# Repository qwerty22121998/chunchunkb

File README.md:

# CHUNCHUN

Wireless split ortholinear keyboard with 70 keys, 2 nice!view displays, 2 rotary encoders.

Original inspirated by Sofle keyboard, but I want to add more keys (F-rows) and ortholinear layout. I also want to add 2 nice!view displays and 2 rotary encoders for better user experience.

## Images

`TBA`

## Specifications

- 70 keys
- 2 nice!view displays (or 4pin OLED)
- 2 rotary encoders (EC11)
- Wireless connection (nice!nano or similar) with ZMK firmware support

## Firmware

[chunchunkb-zmk](https://github.com/qwerty22121998/chunchunkb-zmk)

## Bill of materials
- This only include one side of the keyboard, so you need to double the quantity for the whole keyboard.

| Value                                         | Qty |
|-----------------------------------------------|-----|
| Nice!nano or similar                          | 1   |
| Nice!view or oled                             | 1   |
| SMD 1N4148W                                   | 36  |
| MX Hotswap socket                             | 35  |
| SK6812MINI-E                                  | 35  |
| EC11                                          | 1   |
| MX1.25 Ultra Thin Battery socket (or smiliar) | 1   |
| PCM12 Switch or smiliar                       | 1   |
| Reset switch                                  | 1   |

### Symbols & footprints

- <https://github.com/foostan/kbd>
- <https://github.com/bstiq/nice-nano-kicad>
- <https://github.com/HookyQR/nice_view_pcb>
- <https://github.com/tzarc/reversible-kicad/>
- <https://github.com/keebio/Keebio-Parts.pretty>
- <https://github.com/josefadamcik/SofleKeyboard>

### 3D models

- <https://grabcad.com/library/dip24w-socket-with-ic-1>
- <https://grabcad.com/library/cherry-mx-1>
- <https://grabcad.com/library/mx-cherry-relegendable-keycaps-1>
- <https://grabcad.com/library/ec11-rotary-encoder-dode-switch-15mm-1>
- <https://grabcad.com/library/knobs-15>
- <https://grabcad.com/library/dsa-keycap-for-cherry-mx-switches-1>

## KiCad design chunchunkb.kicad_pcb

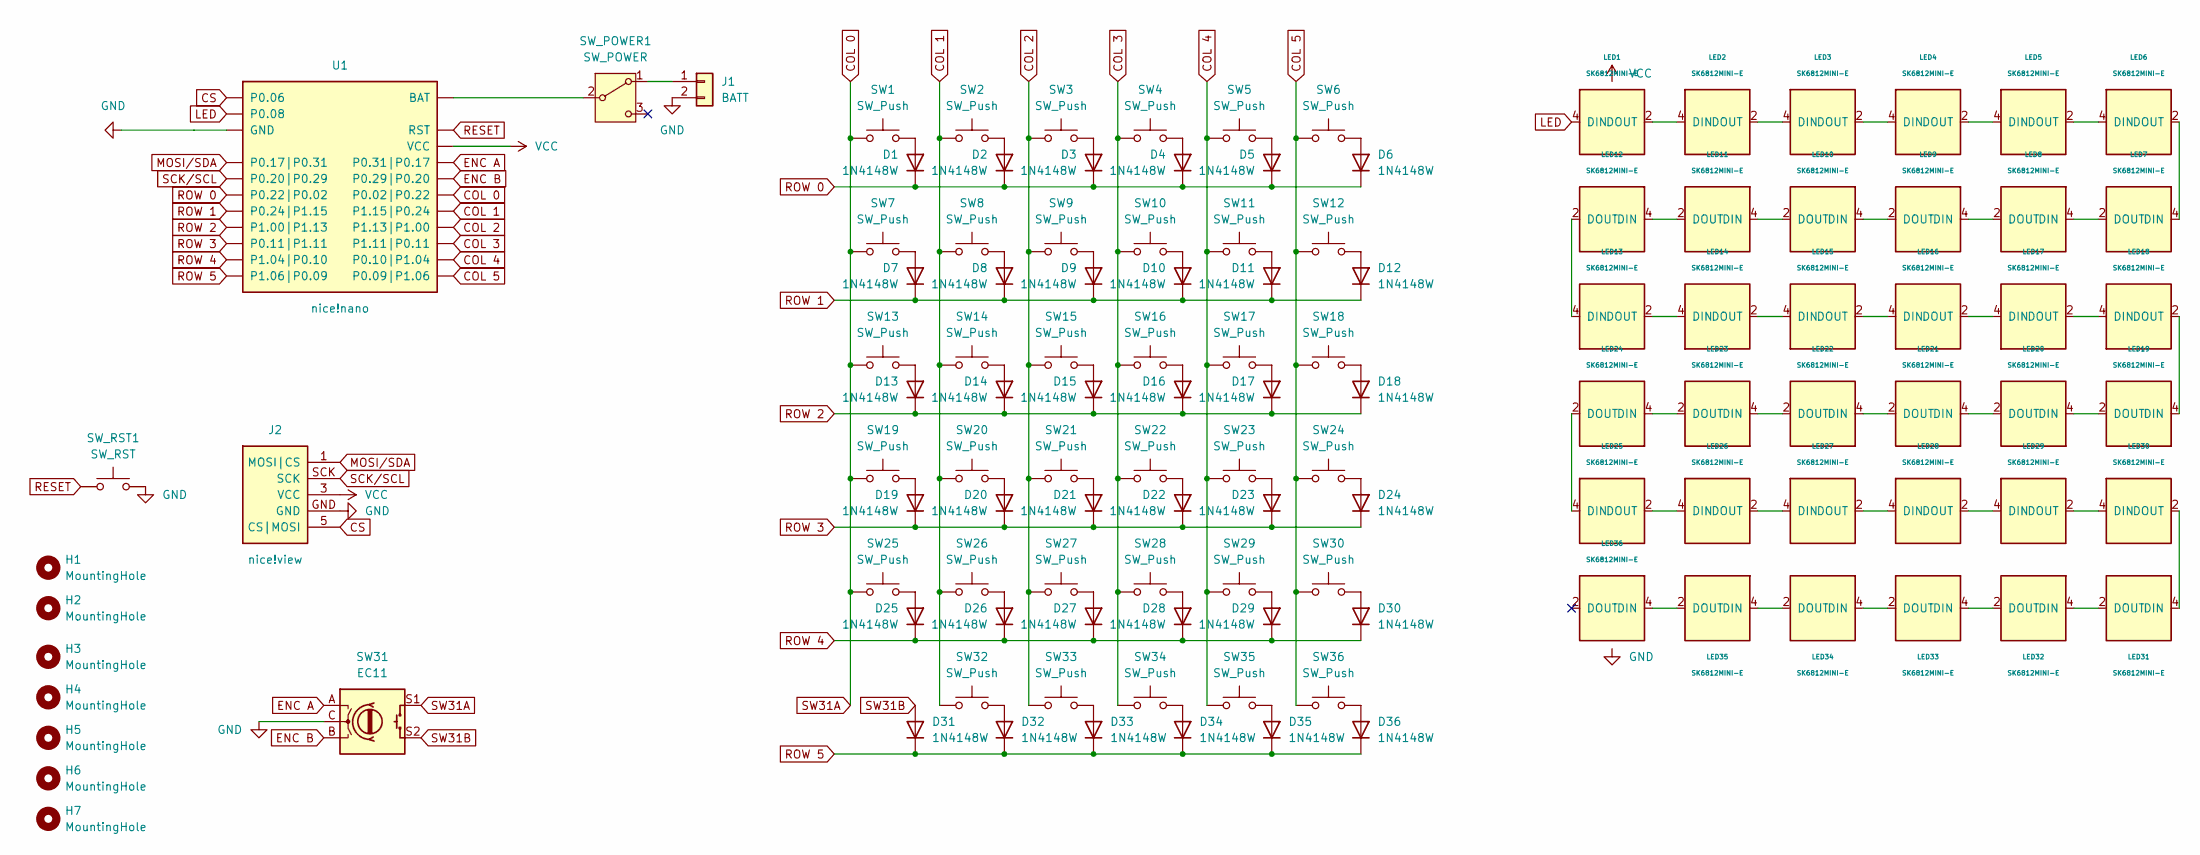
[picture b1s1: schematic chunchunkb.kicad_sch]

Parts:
D1, D2, D3, D4, D5, D6, D7, D8, D9, D10, D11, D12, D13, D14, D15, D16, D17, D18, D19, D20, D21, D22, D23, D24, D25, D26, D27, D28, D29, D30, D31, D32, D33, D34, D35, D36: 1N4148W; CC_D_SOD-123
H1, H2, H3, H4, H5, H6, H7: MountingHole; CC_Hole_4.1mm
J1: BATT; CC_Battery_MX1.25
J2: nice!view; CC_Display_5pin
LED1, LED2, LED3, LED4, LED5, LED6, LED7, LED8, LED9, LED10, LED11, LED12, LED13, LED14, LED15, LED16, LED17, LED18, LED19, LED20, LED21, LED22, LED23, LED24, LED25, LED26, LED27, LED28, LED29, LED30, LED31, LED32, LED33, LED34, LED35, LED36: SK6812MINI-E; CC_SK6812MINI-E
SW1, SW2, SW3, SW4, SW5, SW6, SW7, SW8, SW9, SW10, SW11, SW12, SW13, SW14, SW15, SW16, SW17, SW18, SW19, SW20, SW21, SW22, SW23, SW24, SW25, SW26, SW27, SW28, SW29, SW30, SW32, SW33, SW34, SW35, SW36: SW_Push; CC_MX_Hotswap_1u
SW31: EC11; CC_EC11_MX_1u
SW_POWER1: SW_POWER; CC_SW_Power_PCM12
SW_RST1: SW_RST; CC_SW_Reset
U1: nice!nano; CC_nice_nano

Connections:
COL 0: SW1.1, SW7.1, SW13.1, SW19.1, SW25.1, SW31.S1, U1.18 (P0.02|P0.22)
COL 1: SW2.1, SW8.1, SW14.1, SW20.1, SW26.1, SW32.1, U1.17 (P1.15|P0.24)
COL 2: SW3.1, SW9.1, SW15.1, SW21.1, SW27.1, SW33.1, U1.16 (P1.13|P1.00)
COL 3: SW4.1, SW10.1, SW16.1, SW22.1, SW28.1, SW34.1, U1.15 (P1.11|P0.11)
COL 4: SW5.1, SW11.1, SW17.1, SW23.1, SW29.1, SW35.1, U1.14 (P0.10|P1.04)
COL 5: SW6.1, SW12.1, SW18.1, SW24.1, SW30.1, SW36.1, U1.13 (P0.09|P1.06)
CS: J2.5 (CS|MOSI), U1.P0.06
ENC A: SW31.A, U1.20 (P0.31|P0.17)
ENC B: SW31.B, U1.19 (P0.29|P0.20)
GND: J1.2, J2.GND, LED1.3 (GND), LED2.3 (GND), LED3.3 (GND), LED4.3 (GND), LED5.3 (GND), LED6.3 (GND), LED7.3 (GND), LED8.3 (GND), LED9.3 (GND), LED10.3 (GND), LED11.3 (GND), LED12.3 (GND), LED13.3 (GND), LED14.3 (GND), LED15.3 (GND), LED16.3 (GND), LED17.3 (GND), LED18.3 (GND), LED19.3 (GND), LED20.3 (GND), LED21.3 (GND), LED22.3 (GND), LED23.3 (GND), LED24.3 (GND), LED25.3 (GND), LED26.3 (GND), LED27.3 (GND), LED28.3 (GND), LED29.3 (GND), LED30.3 (GND), LED31.3 (GND), LED32.3 (GND), LED33.3 (GND), LED34.3 (GND), LED35.3 (GND), LED36.3 (GND), SW31.C, SW_RST1.2, U1.GND
LED: LED1.4 (DIN), U1.P0.08
MOSI/SDA: J2.1 (MOSI|CS), U1.5 (P0.17|P0.31)
unnamed: D1.2 (A), SW1.2
unnamed: D2.2 (A), SW2.2
unnamed: D3.2 (A), SW3.2
unnamed: D4.2 (A), SW4.2
unnamed: D5.2 (A), SW5.2
unnamed: D6.2 (A), SW6.2
unnamed: D7.2 (A), SW7.2
unnamed: D8.2 (A), SW8.2
unnamed: D9.2 (A), SW9.2
unnamed: D10.2 (A), SW10.2
unnamed: D11.2 (A), SW11.2
unnamed: D12.2 (A), SW12.2
unnamed: D13.2 (A), SW13.2
unnamed: D14.2 (A), SW14.2
unnamed: D15.2 (A), SW15.2
unnamed: D16.2 (A), SW16.2
unnamed: D17.2 (A), SW17.2
unnamed: D18.2 (A), SW18.2
unnamed: D19.2 (A), SW19.2
unnamed: D20.2 (A), SW20.2
unnamed: D21.2 (A), SW21.2
unnamed: D22.2 (A), SW22.2
unnamed: D23.2 (A), SW23.2
unnamed: D24.2 (A), SW24.2
unnamed: D25.2 (A), SW25.2
unnamed: D26.2 (A), SW26.2
unnamed: D27.2 (A), SW27.2
unnamed: D28.2 (A), SW28.2
unnamed: D29.2 (A), SW29.2
unnamed: D30.2 (A), SW30.2
unnamed: D32.2 (A), SW32.2
unnamed: D33.2 (A), SW33.2
unnamed: D34.2 (A), SW34.2
unnamed: D35.2 (A), SW35.2
unnamed: D36.2 (A), SW36.2
unnamed: J1.1, SW_POWER1.1 (A)
unnamed: LED1.2 (DOUT), LED2.4 (DIN)
unnamed: LED2.2 (DOUT), LED3.4 (DIN)
unnamed: LED3.2 (DOUT), LED4.4 (DIN)
unnamed: LED4.2 (DOUT), LED5.4 (DIN)
unnamed: LED5.2 (DOUT), LED6.4 (DIN)
unnamed: LED6.2 (DOUT), LED7.4 (DIN)
unnamed: LED7.2 (DOUT), LED8.4 (DIN)
unnamed: LED8.2 (DOUT), LED9.4 (DIN)
unnamed: LED9.2 (DOUT), LED10.4 (DIN)
unnamed: LED10.2 (DOUT), LED11.4 (DIN)
unnamed: LED11.2 (DOUT), LED12.4 (DIN)
unnamed: LED12.2 (DOUT), LED13.4 (DIN)
unnamed: LED13.2 (DOUT), LED14.4 (DIN)
unnamed: LED14.2 (DOUT), LED15.4 (DIN)
unnamed: LED15.2 (DOUT), LED16.4 (DIN)
unnamed: LED16.2 (DOUT), LED17.4 (DIN)
unnamed: LED17.2 (DOUT), LED18.4 (DIN)
unnamed: LED18.2 (DOUT), LED19.4 (DIN)
unnamed: LED19.2 (DOUT), LED20.4 (DIN)
unnamed: LED20.2 (DOUT), LED21.4 (DIN)
unnamed: LED21.2 (DOUT), LED22.4 (DIN)
unnamed: LED22.2 (DOUT), LED23.4 (DIN)
unnamed: LED23.2 (DOUT), LED24.4 (DIN)
unnamed: LED24.2 (DOUT), LED25.4 (DIN)
unnamed: LED25.2 (DOUT), LED26.4 (DIN)
unnamed: LED26.2 (DOUT), LED27.4 (DIN)
unnamed: LED27.2 (DOUT), LED28.4 (DIN)
unnamed: LED28.2 (DOUT), LED29.4 (DIN)
unnamed: LED29.2 (DOUT), LED30.4 (DIN)
unnamed: LED30.2 (DOUT), LED31.4 (DIN)
unnamed: LED31.2 (DOUT), LED32.4 (DIN)
unnamed: LED32.2 (DOUT), LED33.4 (DIN)
unnamed: LED33.2 (DOUT), LED34.4 (DIN)
unnamed: LED34.2 (DOUT), LED35.4 (DIN)
unnamed: LED35.2 (DOUT), LED36.4 (DIN)
unnamed: SW_POWER1.2 (B), U1.BAT
RESET: SW_RST1.1, U1.RST
ROW 0: D1.1 (K), D2.1 (K), D3.1 (K), D4.1 (K), D5.1 (K), D6.1 (K), U1.7 (P0.22|P0.02)
ROW 1: D7.1 (K), D8.1 (K), D9.1 (K), D10.1 (K), D11.1 (K), D12.1 (K), U1.8 (P0.24|P1.15)
ROW 2: D13.1 (K), D14.1 (K), D15.1 (K), D16.1 (K), D17.1 (K), D18.1 (K), U1.9 (P1.00|P1.13)
ROW 3: D19.1 (K), D20.1 (K), D21.1 (K), D22.1 (K), D23.1 (K), D24.1 (K), U1.10 (P0.11|P1.11)
ROW 4: D25.1 (K), D26.1 (K), D27.1 (K), D28.1 (K), D29.1 (K), D30.1 (K), U1.11 (P1.04|P0.10)
ROW 5: D31.1 (K), D32.1 (K), D33.1 (K), D34.1 (K), D35.1 (K), D36.1 (K), U1.12 (P1.06|P0.09)
SCK/SCL: J2.SCK, U1.6 (P0.20|P0.29)
SW31B: D31.2 (A), SW31.S2
VCC: J2.3 (VCC), LED1.1 (VCC), LED2.1 (VCC), LED3.1 (VCC), LED4.1 (VCC), LED5.1 (VCC), LED6.1 (VCC), LED7.1 (VCC), LED8.1 (VCC), LED9.1 (VCC), LED10.1 (VCC), LED11.1 (VCC), LED12.1 (VCC), LED13.1 (VCC), LED14.1 (VCC), LED15.1 (VCC), LED16.1 (VCC), LED17.1 (VCC), LED18.1 (VCC), LED19.1 (VCC), LED20.1 (VCC), LED21.1 (VCC), LED22.1 (VCC), LED23.1 (VCC), LED24.1 (VCC), LED25.1 (VCC), LED26.1 (VCC), LED27.1 (VCC), LED28.1 (VCC), LED29.1 (VCC), LED30.1 (VCC), LED31.1 (VCC), LED32.1 (VCC), LED33.1 (VCC), LED34.1 (VCC), LED35.1 (VCC), LED36.1 (VCC), U1.VCC

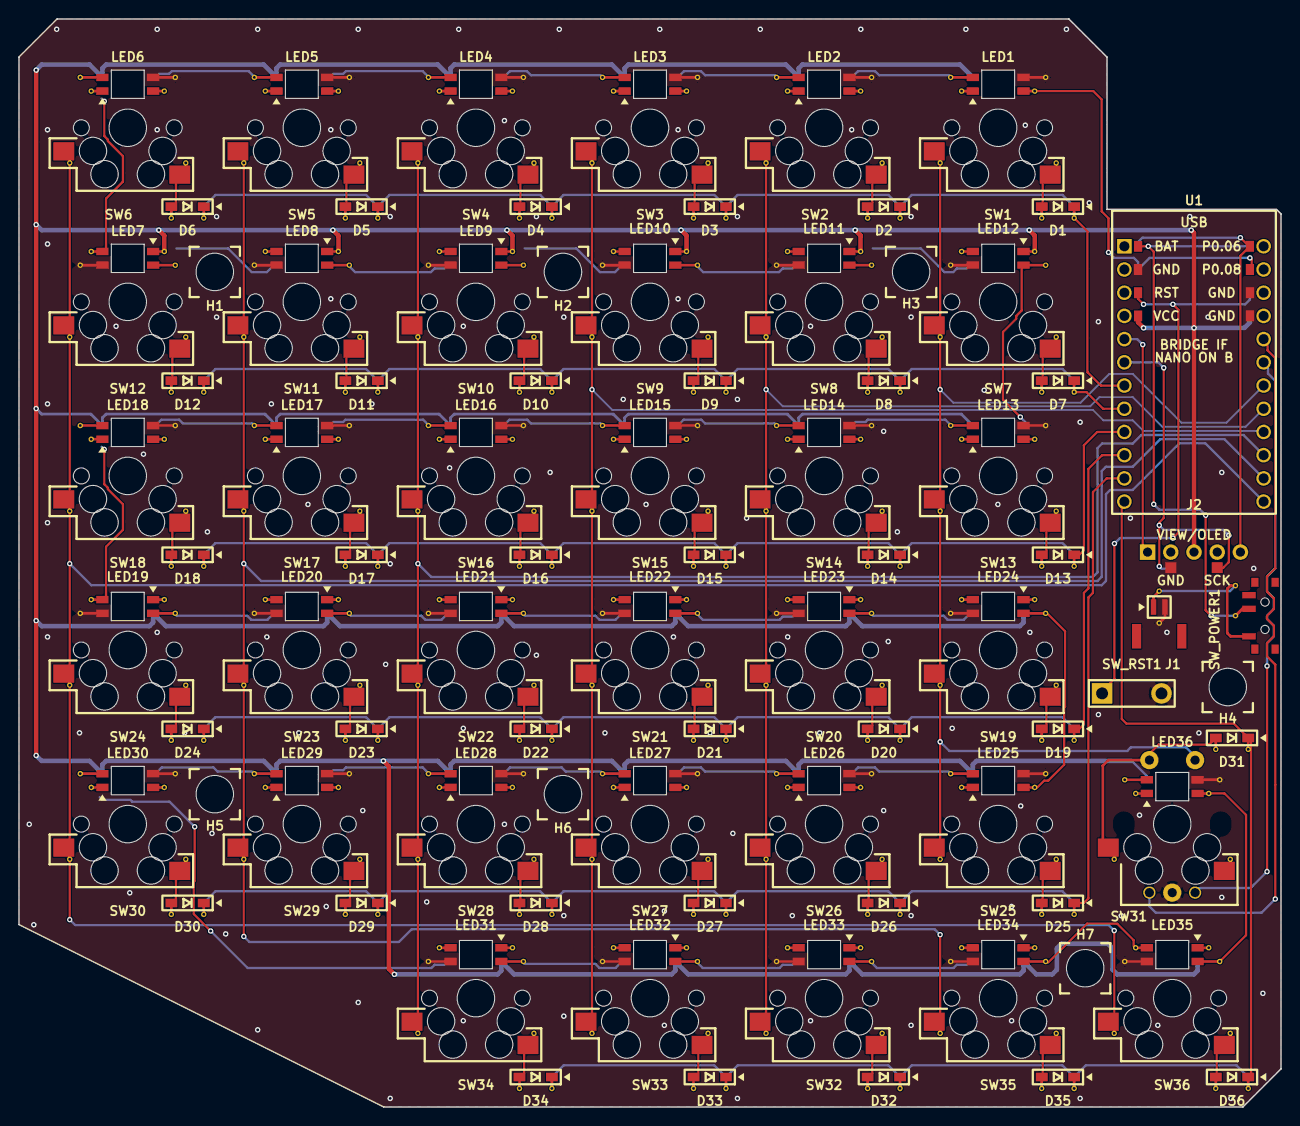
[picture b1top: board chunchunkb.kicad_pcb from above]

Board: 2 copper layers, 138.1 x 119.1 mm, 120 parts (0 on the bottom side), 94 nets.

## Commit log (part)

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2026-03-30 feat: init
2026-03-30 chore: reroute
2026-04-01 dual pcb
2026-04-02 reversible
2026-04-03 reroute
2026-04-03 feat: resize via, rerouting
2026-04-03 fix switch footprint
2026-04-03 fix 3d models
2026-04-03 add screenshot
2026-04-06 feat: add zmk firmware and nice view testing
2026-04-07 feat: add case
2026-04-07 feat: modular layout
2026-04-09 snapshot
2026-04-10 feat: change space btn pos
2026-04-10 chore: wiring
2026-04-20 rev 2
2026-04-20 rem large
